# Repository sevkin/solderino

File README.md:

# Паяльник на Ардуино (тысячи их)

Идея, код, схемы, фото и прочее доступны по лицензии [WTFPL](COPYING.txt)

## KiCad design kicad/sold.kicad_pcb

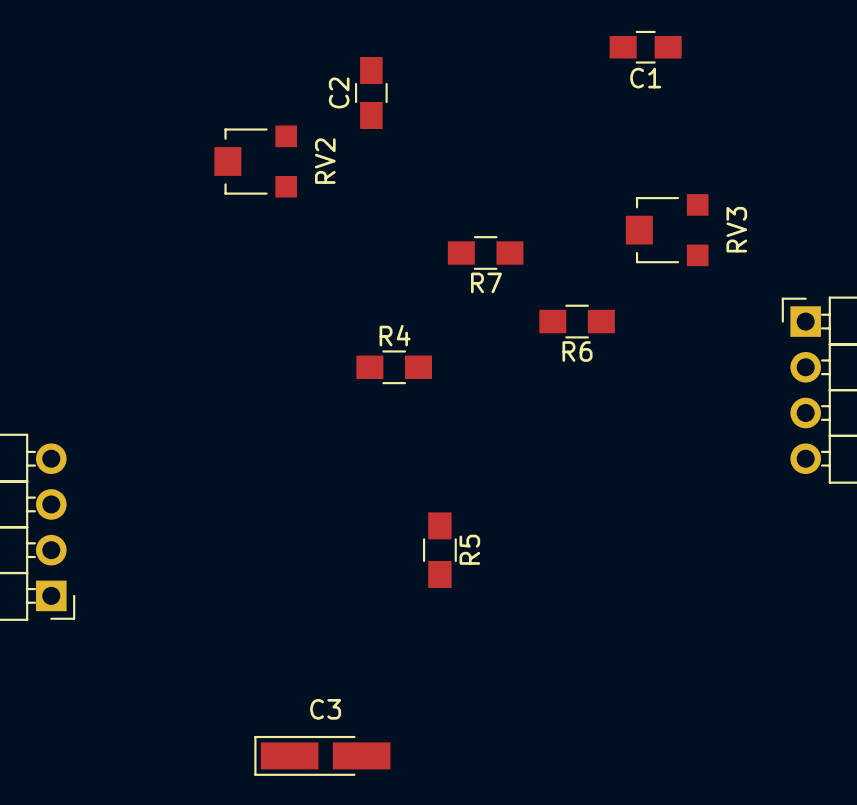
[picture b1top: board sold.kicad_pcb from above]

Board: 2 copper layers, 11 parts (0 on the bottom side), 7 nets, no tracks yet.

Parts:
C1, C2: C; C_0805_HandSoldering
C3: CP; CP_Tantalum_Case-A_EIA-3216-18_Hand
J10, J11: CONN_01X04; Pin_Header_Angled_1x04_Pitch2.54mm
R4, R5, R6, R7: R; R_0805_HandSoldering
RV2, RV3: POT; Potentiometer_Trimmer-EVM3E

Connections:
+5V: C2.1, C3.1, J10.1, R4.1, R5.1
GND: C1.2, C2.2, C3.2, J10.3, J10.4, RV2.2, RV2.3
unnamed: C1.1, R6.1
unnamed: R4.2, R7.2, RV2.1
unnamed: R7.1, RV3.2, RV3.3
TemOUT: J11.3, RV3.1
TermIN: J10.2, R5.2, R6.2

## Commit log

2020-12-24 initial import
